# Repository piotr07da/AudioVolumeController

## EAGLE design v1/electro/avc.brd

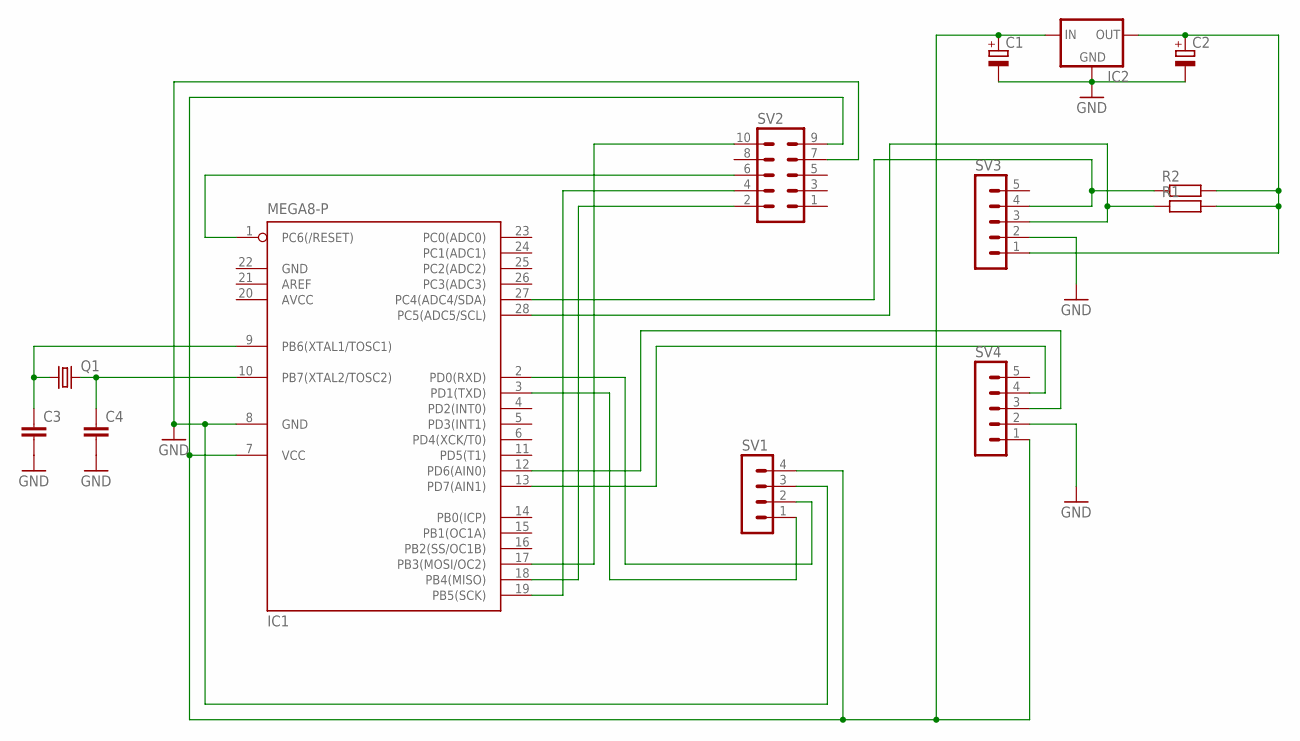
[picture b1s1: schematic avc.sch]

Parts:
C1, C2: CPOL-EUE2.5-5; E2,5-5
C3, C4: C-EU025-025X050; C025-025X050
IC1: MEGA8-P; DIL28-3
IC2: LH0070
Q1: CRYSTALHC49S; HC49/S
R1, R2: R-EU_0207/12; 0207/12
SV1: MA04-1
SV2: MA05-2
SV3, SV4: MA05-1

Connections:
AVCC: IC1.20 (AVCC)
GND: C1.-, C2.-, C3.2, C4.2, IC1.8 (GND), IC1.22 (GND), IC2.GND, SV1.3, SV2.7, SV3.2, SV4.2
unnamed: IC1.2 (PD0(RXD)), SV1.2
unnamed: IC1.3 (PD1(TXD)), SV1.1
unnamed: C3.1, IC1.9 (PB6(XTAL1/TOSC1)), Q1.1
unnamed: IC1.17 (PB3(MOSI/OC2)), SV2.10
unnamed: IC1.18 (PB4(MISO)), SV2.2
unnamed: IC1.1 (PC6(/RESET)), SV2.6
unnamed: IC1.19 (PB5(SCK)), SV2.4
unnamed: C4.1, IC1.10 (PB7(XTAL2/TOSC2)), Q1.2
unnamed: C1.+, IC1.7 (VCC), IC2.IN, SV1.4, SV2.9, SV4.1
unnamed: C2.+, IC2.OUT, R1.2, R2.2, SV3.1
unnamed: IC1.13 (PD7(AIN1)), SV4.4
unnamed: IC1.12 (PD6(AIN0)), SV4.3
unnamed: IC1.27 (PC4(ADC4/SDA)), R2.1, SV3.4
unnamed: IC1.28 (PC5(ADC5/SCL)), R1.1, SV3.3

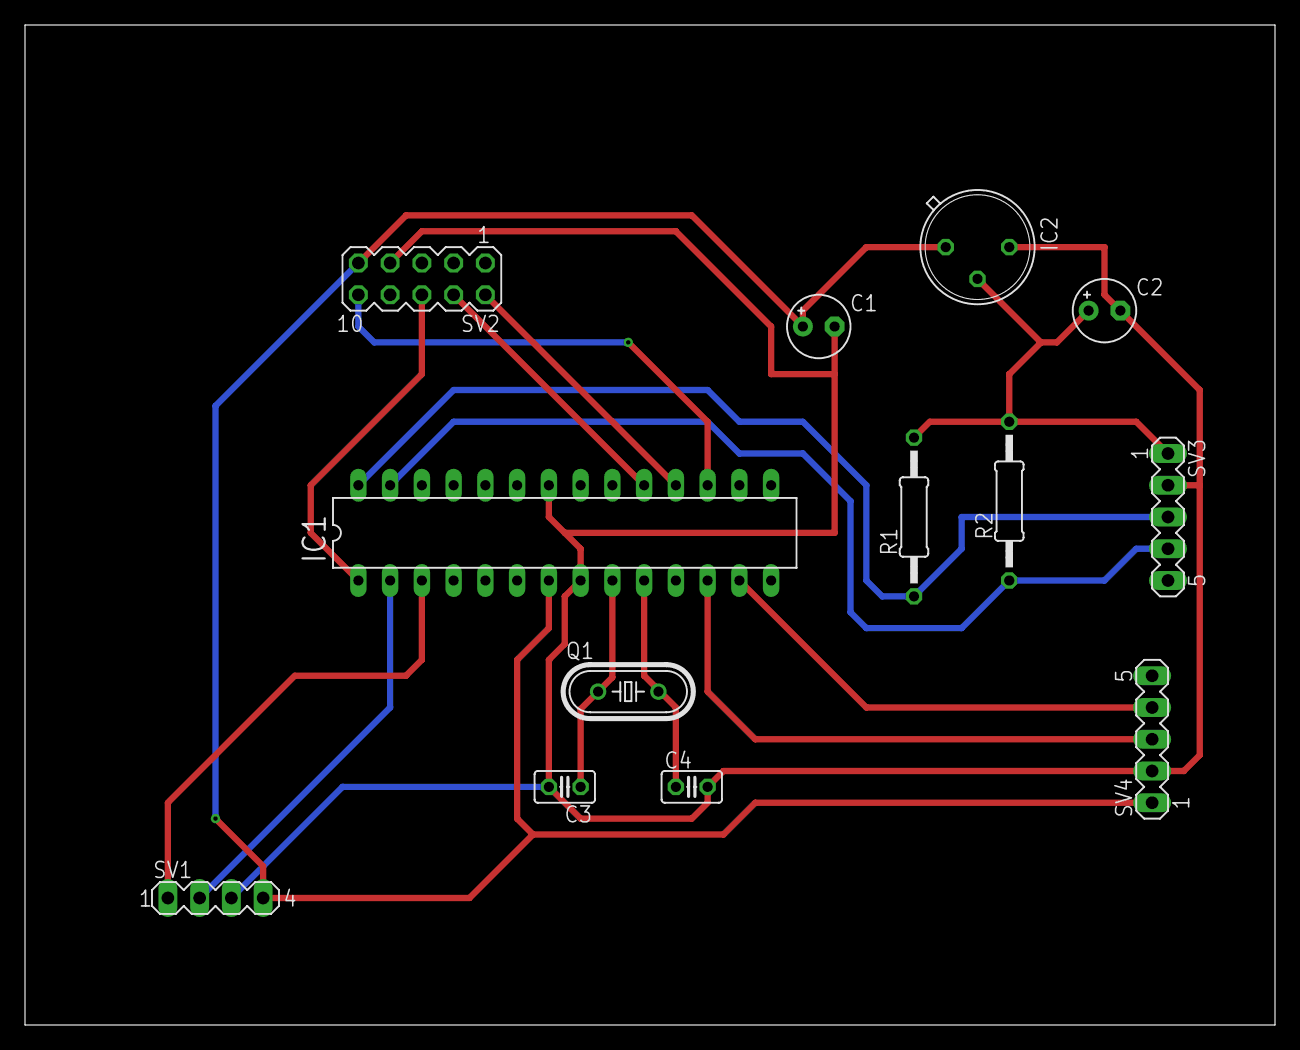
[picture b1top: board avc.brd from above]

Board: 2 copper layers, 100.0 x 80.0 mm, 13 parts (0 on the bottom side), 15 nets.
